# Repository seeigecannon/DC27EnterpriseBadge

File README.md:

# DC27EnterpriseBadge
Enterprise Badge

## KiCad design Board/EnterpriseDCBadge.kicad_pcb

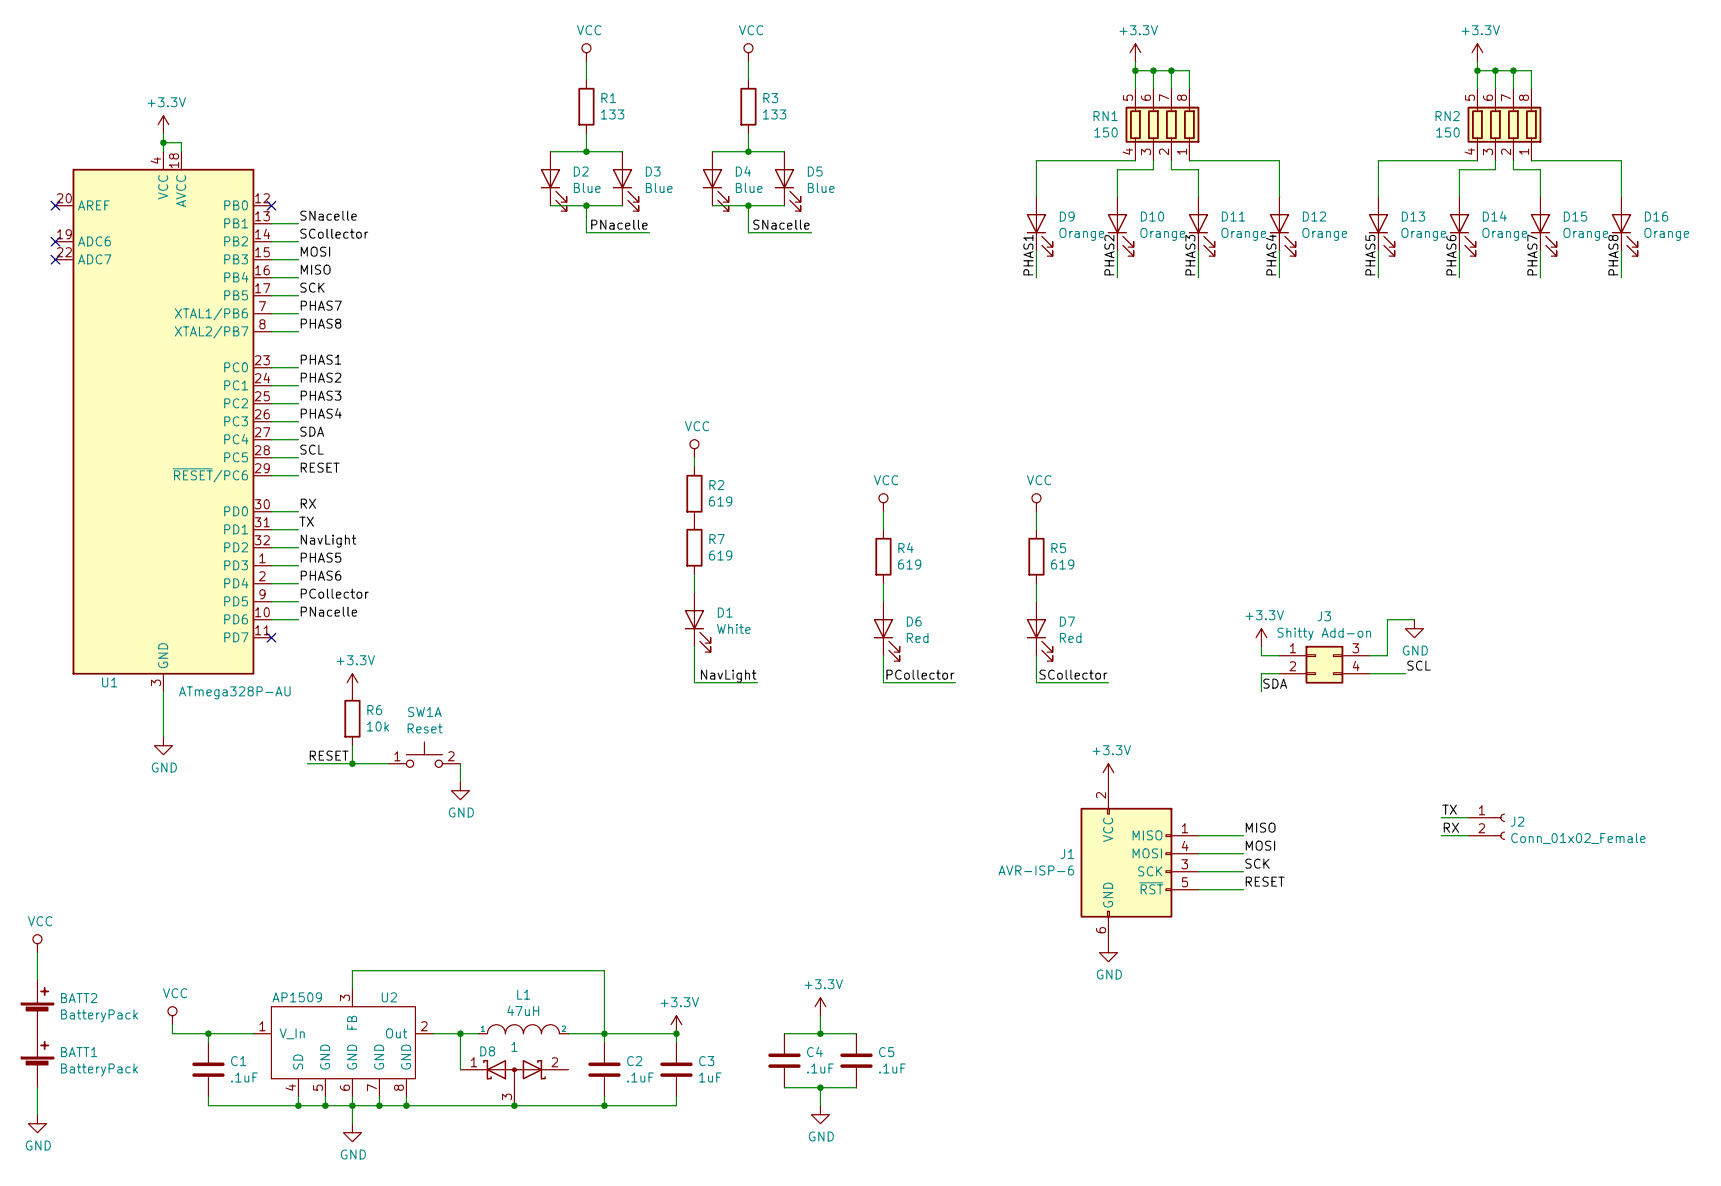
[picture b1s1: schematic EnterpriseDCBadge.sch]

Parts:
BATT1, BATT2: BatteryPack; BatteryHolder_MPD_BC12AAPC_2xAA_noHoles; Part Number BC12AAPC-ND
C1, C2, C4: .1uF; C_1206_3216Metric; Part Number 732-8086-1-ND
C3: 1uF; C_1206_3216Metric; Part Number 732-7685-1-ND
C5: .1uF; C_1206_3216Metric
D1: White; 3.8x1.2mm; Part Number 160-1869-1-ND
D2, D3, D4, D5: Blue; 2PLCC_flipped_noHole; Part Number 1497-1233-1-ND
D6, D7: Red; 2PLCC_flipped_noHole; Part Number 1497-1331-1-ND
D8: 1; SOT-23; Part Number BAS40-06LT1GOSCT-ND
D9, D10, D11, D12, D13, D14, D15, D16: Orange; 2PLCC_flipped_noHole; Part Number 475-2698-1-ND
J1: AVR-ISP-6; PinHeader_2x03_P2.54mm_Vertical; Part Number 609-3210-ND
J2: Conn_01x02_Female; PinHeader_1x02_P2.54mm_Vertical; Part Number 609-4434-ND
J3: Shitty Add-on; PinHeader_2x02_P2.54mm_Vertical; Part Number S7070-ND
L1: 47uH; L_1206_3216Metric_Pad1.42x1.75mm_HandSolder; Part Number 490-12803-1-ND
R1, R3: 133; R_1206_3216Metric; Part Number 311-133FRCT-ND
R2, R4, R5, R7: 619; R_1206_3216Metric; Part Number 311-619FRCT-ND
R6: 10k; R_1206_3216Metric; Part Number RMCF1206FT10K0CT-ND
RN1, RN2: 150; R_Array_Convex_4x1206; Part Number 744C083151JPCT-ND
SW1: Reset; SW_SPST_EVQQ2; Part Number CKN9088CT-ND
U1: ATmega328P-AU; TQFP-32_7x7mm_P0.8mm; Part Number ATMEGA328P-AURCT-ND
U2: AP1509; PowerIntegrations_SO-8; Part Number AP1509-33SGDICT-ND

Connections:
+3V3: C2.1, C3.1, C4.1, C5.1, J1.2 (VCC), J3.1, L1.2, R6.1, RN1.5 (R4.2), RN1.6 (R3.2), RN1.7 (R2.2), RN1.8 (R1.2), RN2.5 (R4.2), RN2.6 (R3.2), RN2.7 (R2.2), RN2.8 (R1.2), U1.4 (VCC), U1.6 (VCC), U1.18 (AVCC), U2.3 (FB)
/MISO: J1.1 (MISO), U1.16 (PB4)
/MOSI: J1.4 (MOSI), U1.15 (PB3)
/NavLight: D1.1 (K), U1.32 (PD2)
/PCollector: D6.1 (K), U1.9 (PD5)
/PHAS1: D9.1 (K), U1.23 (PC0)
/PHAS2: D10.1 (K), U1.24 (PC1)
/PHAS3: D11.1 (K), U1.25 (PC2)
/PHAS4: D12.1 (K), U1.26 (PC3)
/PHAS5: D13.1 (K), U1.1 (PD3)
/PHAS6: D14.1 (K), U1.2 (PD4)
/PHAS7: D15.1 (K), U1.7 (XTAL1/PB6)
/PHAS8: D16.1 (K), U1.8 (XTAL2/PB7)
/PNacelle: D2.1 (K), D3.1 (K), U1.10 (PD6)
/RESET: J1.5 (~RST), R6.2, SW1.1 (A), U1.29 (~RESET~/PC6)
/RX: J2.2, U1.30 (PD0)
/SCK: J1.3 (SCK), U1.17 (PB5)
/SCL: J3.4, U1.28 (PC5)
/SCollector: D7.1 (K), U1.14 (PB2)
/SDA: J3.2, U1.27 (PC4)
/SNacelle: D4.1 (K), D5.1 (K), U1.13 (PB1)
/TX: J2.1, U1.31 (PD1)
GND: BATT1.2 (-), C1.2, C2.2, C3.2, C4.2, C5.2, D8.3 (A), J1.6 (GND), J3.3, SW1.2 (B), U1.3 (GND), U1.5 (GND), U1.21 (GND), U2.4 (SD), U2.5 (GND), U2.6 (GND), U2.7 (GND), U2.8 (GND)
unnamed: BATT1.1 (+), BATT2.2 (-)
unnamed: D1.2 (A), R7.2
unnamed: D2.2 (A), D3.2 (A), R1.2
unnamed: D4.2 (A), D5.2 (A), R3.2
unnamed: D6.2 (A), R4.2
unnamed: D7.2 (A), R5.2
unnamed: D8.1 (K), L1.1, U2.2 (Out)
unnamed: D9.2 (A), RN1.4 (R4.1)
unnamed: D10.2 (A), RN1.3 (R3.1)
unnamed: D11.2 (A), RN1.2 (R2.1)
unnamed: D12.2 (A), RN1.1 (R1.1)
unnamed: D13.2 (A), RN2.4 (R4.1)
unnamed: D14.2 (A), RN2.3 (R3.1)
unnamed: D15.2 (A), RN2.2 (R2.1)
unnamed: D16.2 (A), RN2.1 (R1.1)
unnamed: R2.2, R7.1
VCC: BATT2.1 (+), C1.1, R1.1, R2.1, R3.1, R4.1, R5.1, U2.1 (V_In)

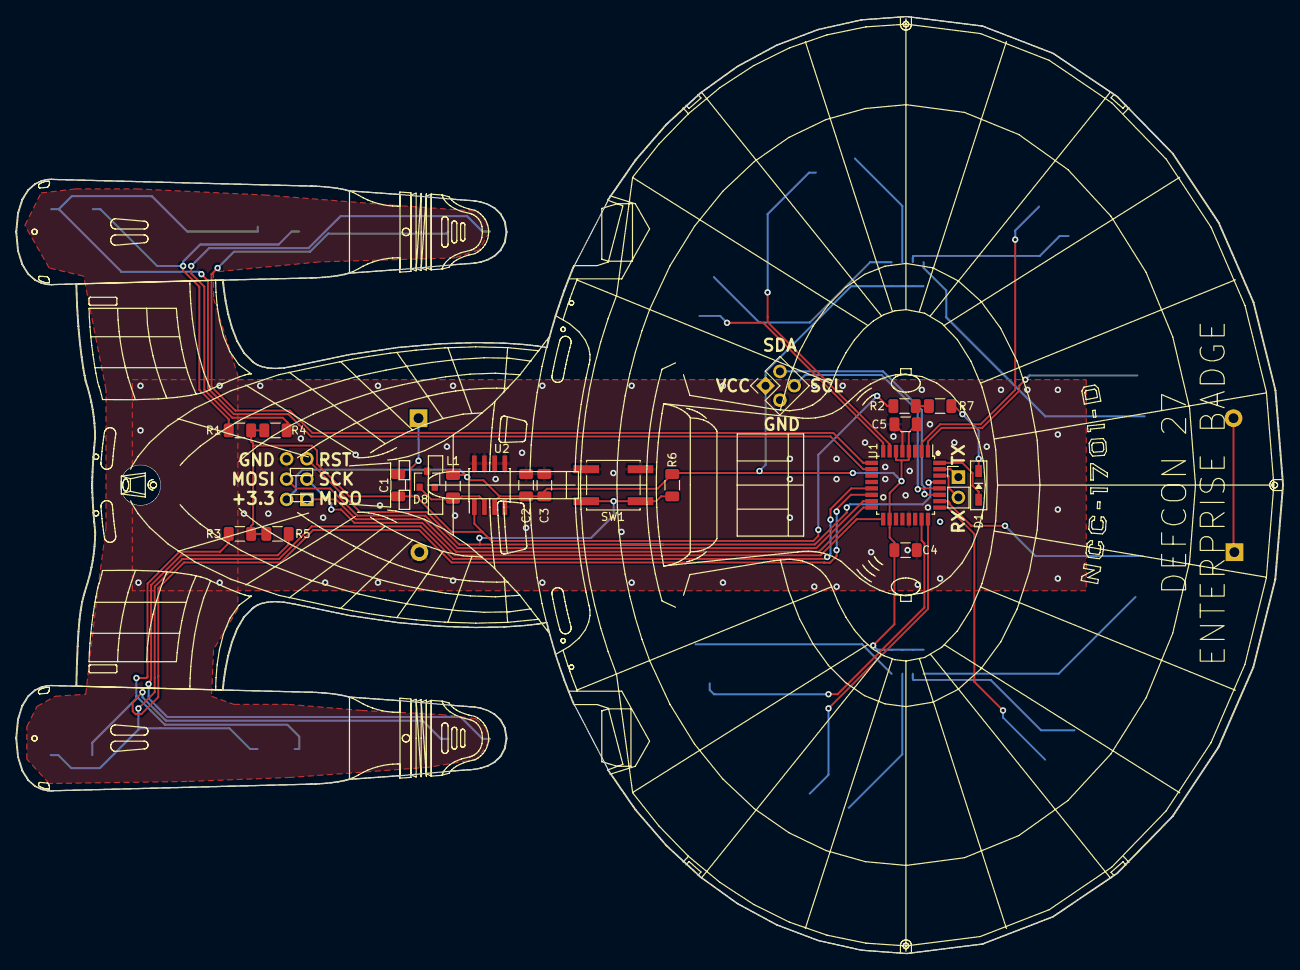
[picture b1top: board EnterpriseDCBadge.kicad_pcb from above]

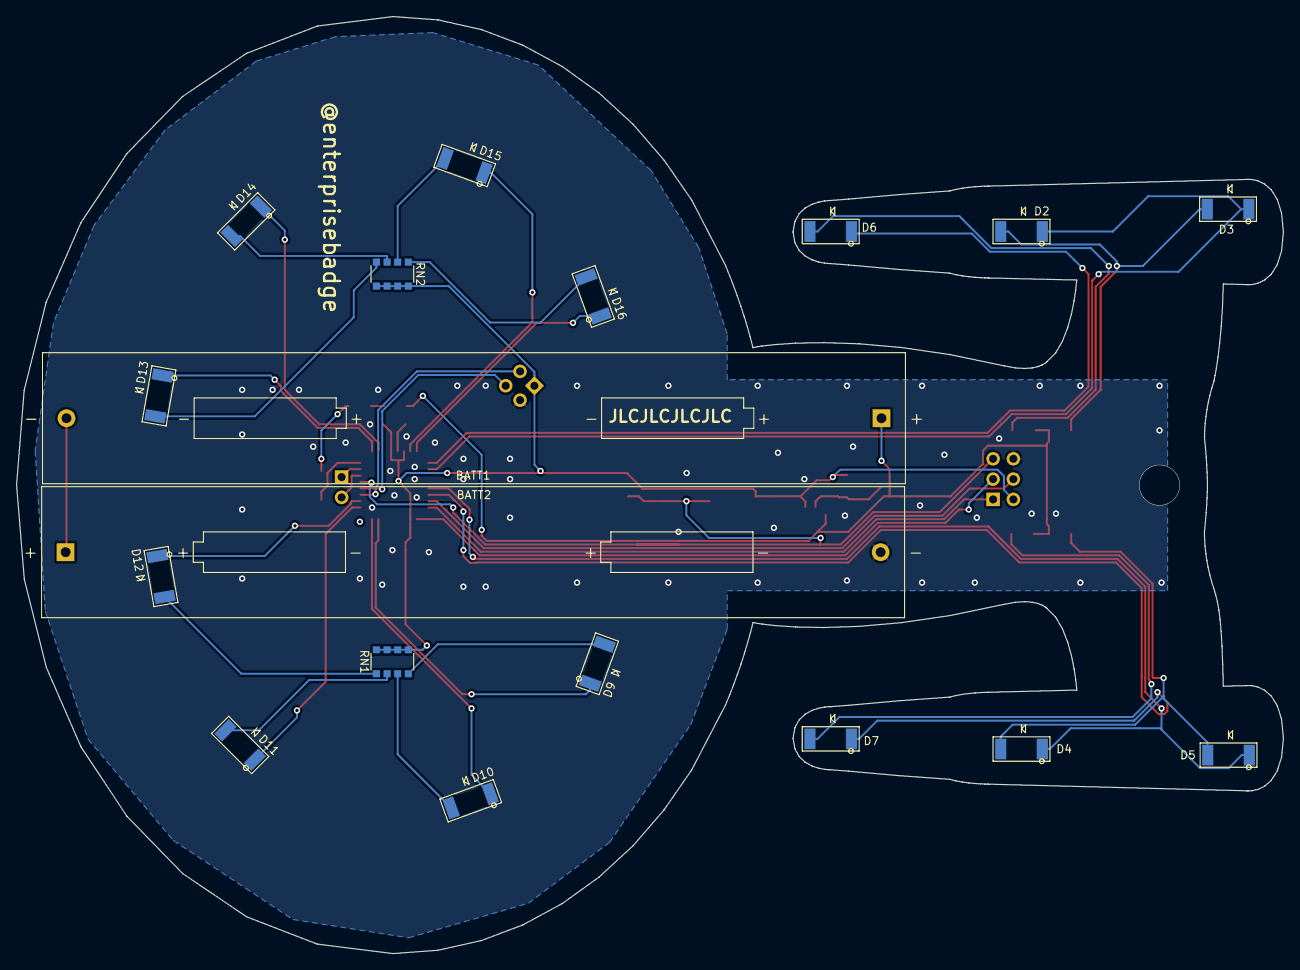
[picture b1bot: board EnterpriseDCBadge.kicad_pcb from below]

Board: 2 copper layers, 158.6 x 117.3 mm, 39 parts (18 on the bottom side), 40 nets.

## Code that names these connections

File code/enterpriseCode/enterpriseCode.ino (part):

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unsigned int boardMode;     //modes: normal phaser, binary counter, larson scanner, disco

uint8_t otherLEDs=B0000000;    //0,0,0,PNacelle,PCollector/NavLight/SCollector,SNacelle
const uint8_t PNacelle     = 0b00010000;
const uint8_t PCollector   = 0b00001000;
const uint8_t NavLight     = 0b00000100;
const uint8_t SCollector   = 0b00000010;
const uint8_t SNacelle     = 0b00000001;
unsigned short phaserCounter=0;
byte larsonScanner=B00000001;
bool larsonScannerDirection=false;
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//   bit 1: SCollector
//   bit 0: SNacelle
void setOtherLEDs() {
    // PNacelle = PD6
    // PCollector = PD5
    // NavLight = PD2
    // SCollector = PB2
    // SNacelle = PB1
	static const uint8_t DDRDMask = 0b01100100;
	static const uint8_t DDRBMask = 0b00000110;
    bool pNacelle = otherLEDs & PNacelle;
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}

void setPhasers(uint8_t phaserMask) {
    //PHAS1=PC0
    //PHAS2=PC1
    //PHAS3=PC2
    //PHAS4=PC3
    //PHAS5=PD3
    //PHAS6=PD4
    //PHAS7=PB6
    //PHAS8=PB7
	static const uint8_t DDRBMask = 0b11000000;
	static const uint8_t DDRCMask = 0b00001111;
	static const uint8_t DDRDMask = 0b00110000;
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
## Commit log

2019-08-08 Create temp
2019-08-08 Add files via upload
    Sorry about the mess...
2021-08-10 Add files via upload
    Updated BOM to actually include part numbers.
